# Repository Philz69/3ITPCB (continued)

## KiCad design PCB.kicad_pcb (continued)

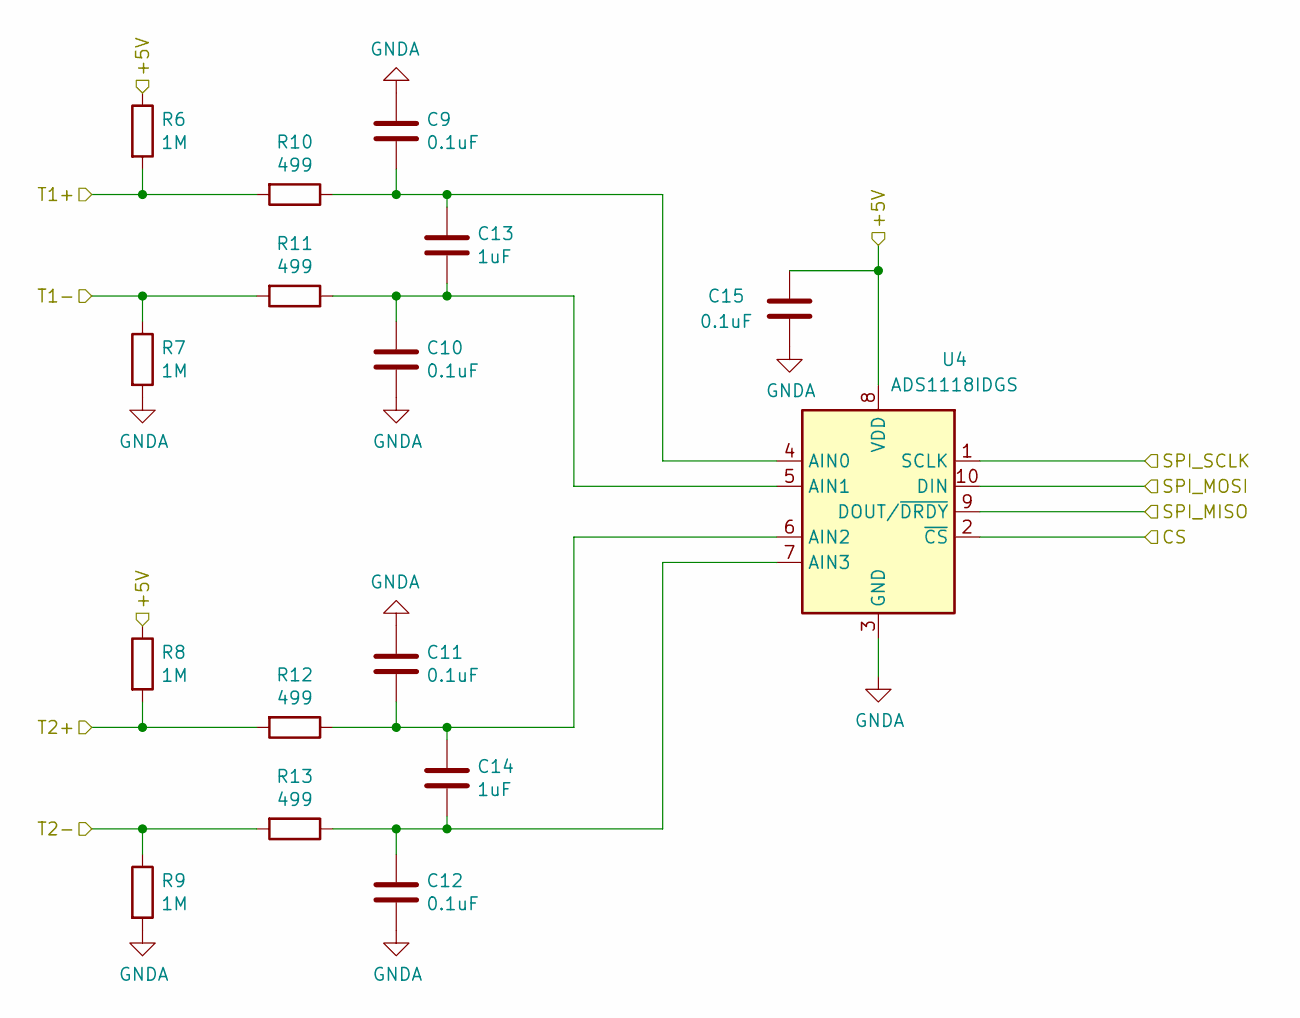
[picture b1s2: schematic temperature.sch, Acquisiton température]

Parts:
C9, C10, C11, C12, C15: 0.1uF; C_0402_1005Metric
C13, C14: 1uF; C_0402_1005Metric
R6, R7, R8, R9: 1M; R_0805_2012Metric
R10, R11, R12, R13: 499; R_0603_1608Metric
U4: ADS1118IDGS; VSSOP-10_3x3mm_P0.5mm

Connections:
/+5V: C15.2, R6.1, R8.1, U4.8 (VDD); also elsewhere on the board
/CS1: U4.2 (~CS); also elsewhere on the board
/MISO: U4.9 (DOUT/~DRDY); also elsewhere on the board
/MOSI: U4.10 (DIN); also elsewhere on the board
/SCK: U4.1 (SCLK); also elsewhere on the board
/T1+: R6.2, R10.2; also elsewhere on the board
/T1-: R7.1, R11.2; also elsewhere on the board
/T2+: R8.2, R12.2; also elsewhere on the board
/T2-: R9.1, R13.2; also elsewhere on the board
GNDA: C9.2, C10.2, C11.2, C12.2, C15.1, R7.2, R9.2, U4.3 (GND); also elsewhere on the board
unnamed: C10.1, C13.2, R11.1, U4.5 (AIN1)
unnamed: C11.1, C14.1, R12.1, U4.6 (AIN2)
unnamed: C12.1, C14.2, R13.1, U4.7 (AIN3)
unnamed: C9.1, C13.1, R10.1, U4.4 (AIN0)

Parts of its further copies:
C16, C17, C18, C19, C22, C23, C24, C25, C26, C29, C30, C31, C32, C33, C36, C71, C72, C73, C74, C77, C78, C79, C80, C81, C84, C85, C86, C87, C88, C91, C92, C93, C94, C95, C98: 0.1uF; C_0402_1005Metric
C20, C21, C27, C28, C34, C35, C75, C76, C82, C83, C89, C90, C96, C97: 1uF; C_0402_1005Metric
R14, R15, R16, R17, R22, R23, R24, R25, R30, R31, R32, R33, R94, R95, R96, R97, R102, R103, R104, R105, R110, R111, R112, R113, R118, R119, R120, R121: 1M; R_0805_2012Metric
R18, R19, R20, R21, R26, R27, R28, R29, R34, R35, R36, R37, R98, R99, R100, R101, R106, R107, R108, R109, R114, R115, R116, R117, R122, R123, R124, R125: 499; R_0603_1608Metric
U5, U6, U7, U32, U33, U34, U35: ADS1118IDGS; VSSOP-10_3x3mm_P0.5mm

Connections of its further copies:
/+5V: C22.2, C29.2, C36.2, C77.2, C84.2, C91.2, C98.2, R14.1, R16.1, R22.1, R24.1, R30.1, R32.1, R94.1, R96.1, R102.1, R104.1, R110.1, R112.1, R118.1, R120.1, U5.8 (VDD), U6.8 (VDD), U7.8 (VDD), U32.8 (VDD), U33.8 (VDD), U34.8 (VDD), U35.8 (VDD); also elsewhere on the board
/CS2: U5.2 (~CS); also elsewhere on the board
/CS3: U6.2 (~CS); also elsewhere on the board
/CS4: U7.2 (~CS); also elsewhere on the board
/CS5: U32.2 (~CS); also elsewhere on the board
/CS6: U33.2 (~CS); also elsewhere on the board
/CS7: U34.2 (~CS); also elsewhere on the board
/CS8: U35.2 (~CS); also elsewhere on the board
/MISO: U5.9 (DOUT/~DRDY), U6.9 (DOUT/~DRDY), U7.9 (DOUT/~DRDY), U32.9 (DOUT/~DRDY), U33.9 (DOUT/~DRDY), U34.9 (DOUT/~DRDY), U35.9 (DOUT/~DRDY); also elsewhere on the board
/MOSI: U5.10 (DIN), U6.10 (DIN), U7.10 (DIN), U32.10 (DIN), U33.10 (DIN), U34.10 (DIN), U35.10 (DIN); also elsewhere on the board
/SCK: U5.1 (SCLK), U6.1 (SCLK), U7.1 (SCLK), U32.1 (SCLK), U33.1 (SCLK), U34.1 (SCLK), U35.1 (SCLK); also elsewhere on the board
/T3+: R14.2, R18.2; also elsewhere on the board
/T3-: R15.1, R19.2; also elsewhere on the board
/T4+: R16.2, R20.2; also elsewhere on the board
/T4-: R17.1, R21.2; also elsewhere on the board
/T5+: R22.2, R26.2; also elsewhere on the board
/T5-: R23.1, R27.2; also elsewhere on the board
/T6+: R24.2, R28.2; also elsewhere on the board
/T6-: R25.1, R29.2; also elsewhere on the board
/T7+: R30.2, R34.2; also elsewhere on the board
/T7-: R31.1, R35.2; also elsewhere on the board
/T8+: R32.2, R36.2; also elsewhere on the board
/T8-: R33.1, R37.2; also elsewhere on the board
/T9+: R94.2, R98.2; also elsewhere on the board
/T9-: R95.1, R99.2; also elsewhere on the board
/T10+: R96.2, R100.2; also elsewhere on the board
/T10-: R97.1, R101.2; also elsewhere on the board
/T11+: R102.2, R106.2; also elsewhere on the board
/T11-: R103.1, R107.2; also elsewhere on the board
/T12+: R104.2, R108.2; also elsewhere on the board
/T12-: R105.1, R109.2; also elsewhere on the board
/T13+: R110.2, R114.2; also elsewhere on the board
/T13-: R111.1, R115.2; also elsewhere on the board
/T14+: R112.2, R116.2; also elsewhere on the board
/T14-: R113.1, R117.2; also elsewhere on the board
/T15+: R118.2, R122.2; also elsewhere on the board
/T15-: R119.1, R123.2; also elsewhere on the board
/T16+: R120.2, R124.2; also elsewhere on the board
/T16-: R121.1, R125.2; also elsewhere on the board
GNDA: C16.2, C17.2, C18.2, C19.2, C22.1, C23.2, C24.2, C25.2, C26.2, C29.1, C30.2, C31.2, C32.2, C33.2, C36.1, C71.2, C72.2, C73.2, C74.2, C77.1, C78.2, C79.2, C80.2, C81.2, C84.1, C85.2, C86.2, C87.2, C88.2, C91.1, C92.2, C93.2, C94.2, C95.2, C98.1, R15.2, R17.2, R23.2, R25.2, R31.2, R33.2, R95.2, R97.2, R103.2, R105.2, R111.2, R113.2, R119.2, R121.2, U5.3 (GND), U6.3 (GND), U7.3 (GND), U32.3 (GND), U33.3 (GND), U34.3 (GND), U35.3 (GND); also elsewhere on the board
unnamed: C16.1, C20.1, R18.1, U5.4 (AIN0)
unnamed: C17.1, C20.2, R19.1, U5.5 (AIN1)
unnamed: C18.1, C21.1, R20.1, U5.6 (AIN2)
unnamed: C19.1, C21.2, R21.1, U5.7 (AIN3)
unnamed: C23.1, C27.1, R26.1, U6.4 (AIN0)
unnamed: C24.1, C27.2, R27.1, U6.5 (AIN1)
unnamed: C25.1, C28.1, R28.1, U6.6 (AIN2)
unnamed: C26.1, C28.2, R29.1, U6.7 (AIN3)
unnamed: C30.1, C34.1, R34.1, U7.4 (AIN0)
unnamed: C31.1, C34.2, R35.1, U7.5 (AIN1)
unnamed: C32.1, C35.1, R36.1, U7.6 (AIN2)
unnamed: C33.1, C35.2, R37.1, U7.7 (AIN3)
unnamed: C71.1, C75.1, R98.1, U32.4 (AIN0)
unnamed: C72.1, C75.2, R99.1, U32.5 (AIN1)
unnamed: C73.1, C76.1, R100.1, U32.6 (AIN2)
unnamed: C74.1, C76.2, R101.1, U32.7 (AIN3)
unnamed: C78.1, C82.1, R106.1, U33.4 (AIN0)
unnamed: C79.1, C82.2, R107.1, U33.5 (AIN1)
unnamed: C80.1, C83.1, R108.1, U33.6 (AIN2)
unnamed: C81.1, C83.2, R109.1, U33.7 (AIN3)
unnamed: C85.1, C89.1, R114.1, U34.4 (AIN0)
unnamed: C86.1, C89.2, R115.1, U34.5 (AIN1)
unnamed: C87.1, C90.1, R116.1, U34.6 (AIN2)
unnamed: C88.1, C90.2, R117.1, U34.7 (AIN3)
unnamed: C92.1, C96.1, R122.1, U35.4 (AIN0)
unnamed: C93.1, C96.2, R123.1, U35.5 (AIN1)
unnamed: C94.1, C97.1, R124.1, U35.6 (AIN2)
unnamed: C95.1, C97.2, R125.1, U35.7 (AIN3)

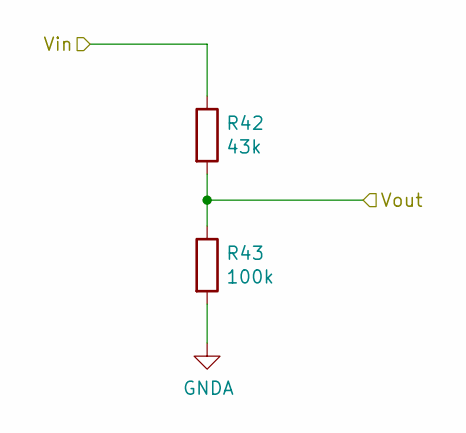
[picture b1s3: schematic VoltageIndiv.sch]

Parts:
R38: 43k; R_0805_2012Metric
R39: 100k; R_0805_2012Metric

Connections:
/A0: R38.2, R39.1; also elsewhere on the board
/VinPassif1: R38.1; also elsewhere on the board
GNDA: R39.2; also elsewhere on the board

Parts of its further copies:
R40, R42, R44, R46, R48, R50, R52, R66, R68, R70, R72, R74, R76, R78, R80: 43k; R_0805_2012Metric
R41, R43, R45, R47, R49, R51, R53, R67, R69, R71, R73, R75, R77, R79, R81: 100k; R_0805_2012Metric

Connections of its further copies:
/A1: R40.2, R41.1; also elsewhere on the board
/A2: R42.2, R43.1; also elsewhere on the board
/A3: R44.2, R45.1; also elsewhere on the board
/A4: R46.2, R47.1; also elsewhere on the board
/A5: R48.2, R49.1; also elsewhere on the board
/A6: R50.2, R51.1; also elsewhere on the board
/A7: R52.2, R53.1; also elsewhere on the board
/A8: R66.2, R67.1; also elsewhere on the board
/A9: R68.2, R69.1; also elsewhere on the board
/A10: R70.2, R71.1; also elsewhere on the board
/A11: R72.2, R73.1; also elsewhere on the board
/A12: R74.2, R75.1; also elsewhere on the board
/A13: R76.2, R77.1; also elsewhere on the board
/A14: R78.2, R79.1; also elsewhere on the board
/A15: R80.2, R81.1; also elsewhere on the board
/VinActif1: R66.1; also elsewhere on the board
/VinActif2: R68.1; also elsewhere on the board
/VinActif3: R70.1; also elsewhere on the board
/VinActif4: R72.1; also elsewhere on the board
/VinActif5: R74.1; also elsewhere on the board
/VinActif6: R76.1; also elsewhere on the board
/VinActif7: R78.1; also elsewhere on the board
/VinActif8: R80.1; also elsewhere on the board
/VinPassif2: R40.1; also elsewhere on the board
/VinPassif3: R42.1; also elsewhere on the board
/VinPassif4: R44.1; also elsewhere on the board
/VinPassif5: R46.1; also elsewhere on the board
/VinPassif6: R48.1; also elsewhere on the board
/VinPassif7: R50.1; also elsewhere on the board
/VinPassif8: R52.1; also elsewhere on the board
GNDA: R41.2, R43.2, R45.2, R47.2, R49.2, R51.2, R53.2, R67.2, R69.2, R71.2, R73.2, R75.2, R77.2, R79.2, R81.2; also elsewhere on the board

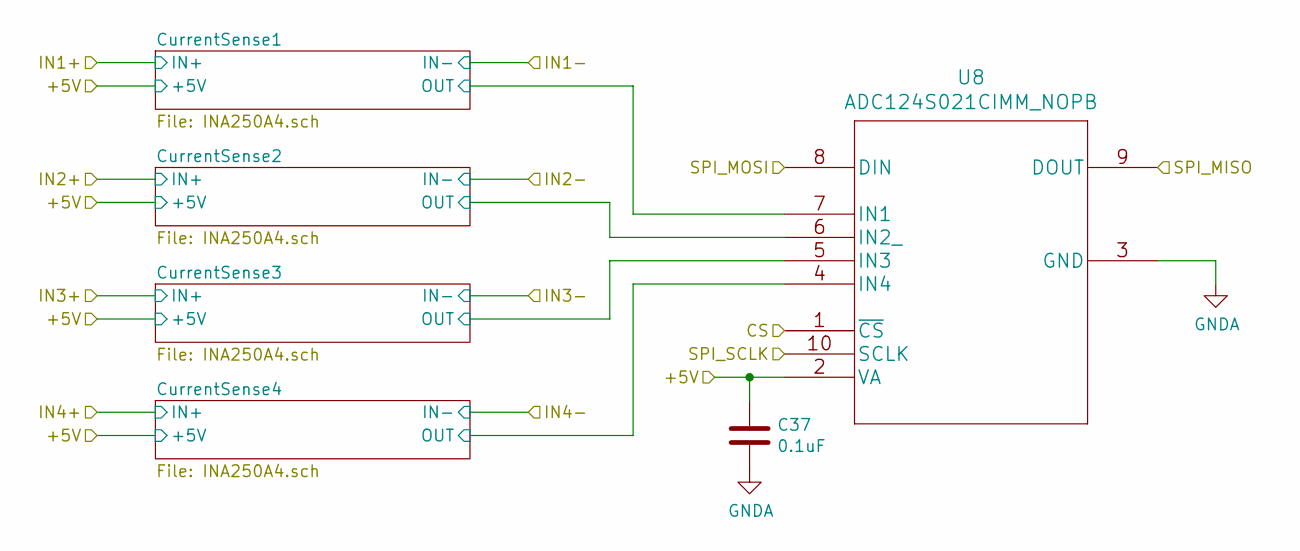
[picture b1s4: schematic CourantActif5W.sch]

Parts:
C52: 0.1uF; C_0402_1005Metric
U23: ADC124S021CIMM_NOPB; VSSOP-10_3x3mm_P0.5mm

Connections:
/+5V: C52.1, U23.2 (VA); also elsewhere on the board
/CS9: U23.1 (~CS); also elsewhere on the board
/CourantIndiv1/CurrentSense1/OUT: U23.7 (IN1); also elsewhere on the board
/CourantIndiv1/CurrentSense2/OUT: U23.6 (IN2_); also elsewhere on the board
/CourantIndiv1/CurrentSense3/OUT: U23.5 (IN3); also elsewhere on the board
/CourantIndiv1/CurrentSense4/OUT: U23.4 (IN4); also elsewhere on the board
/MISO: U23.9 (DOUT); also elsewhere on the board
/MOSI: U23.8 (DIN); also elsewhere on the board
/SCK: U23.10 (SCLK); also elsewhere on the board
GNDA: C52.2, U23.3 (GND); also elsewhere on the board

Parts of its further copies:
C37, C42, C47: 0.1uF; C_0402_1005Metric
U8, U13, U18: ADC124S021CIMM_NOPB; VSSOP-10_3x3mm_P0.5mm

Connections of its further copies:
/+5V: C37.1, C42.1, C47.1, U8.2 (VA), U13.2 (VA), U18.2 (VA); also elsewhere on the board
/CS10: U8.1 (~CS); also elsewhere on the board
/CS11: U13.1 (~CS); also elsewhere on the board
/CS12: U18.1 (~CS); also elsewhere on the board
/CourantActif5W1/CurrentSense1/OUT: U13.7 (IN1); also elsewhere on the board
/CourantActif5W1/CurrentSense2/OUT: U13.6 (IN2_); also elsewhere on the board
/CourantActif5W1/CurrentSense3/OUT: U13.5 (IN3); also elsewhere on the board
/CourantActif5W1/CurrentSense4/OUT: U13.4 (IN4); also elsewhere on the board
/CourantActif5W2/CurrentSense1/OUT: U18.7 (IN1); also elsewhere on the board
/CourantActif5W2/CurrentSense2/OUT: U18.6 (IN2_); also elsewhere on the board
/CourantActif5W2/CurrentSense3/OUT: U18.5 (IN3); also elsewhere on the board
/CourantActif5W2/CurrentSense4/OUT: U18.4 (IN4); also elsewhere on the board
/CourantIndiv2/CurrentSense1/OUT: U8.7 (IN1); also elsewhere on the board
/CourantIndiv2/CurrentSense2/OUT: U8.6 (IN2_); also elsewhere on the board
/CourantIndiv2/CurrentSense3/OUT: U8.5 (IN3); also elsewhere on the board
/CourantIndiv2/CurrentSense4/OUT: U8.4 (IN4); also elsewhere on the board
/MISO: U8.9 (DOUT), U13.9 (DOUT), U18.9 (DOUT); also elsewhere on the board
/MOSI: U8.8 (DIN), U13.8 (DIN), U18.8 (DIN); also elsewhere on the board
/SCK: U8.10 (SCLK), U13.10 (SCLK), U18.10 (SCLK); also elsewhere on the board
GNDA: C37.2, C42.2, C47.2, U8.3 (GND), U13.3 (GND), U18.3 (GND); also elsewhere on the board

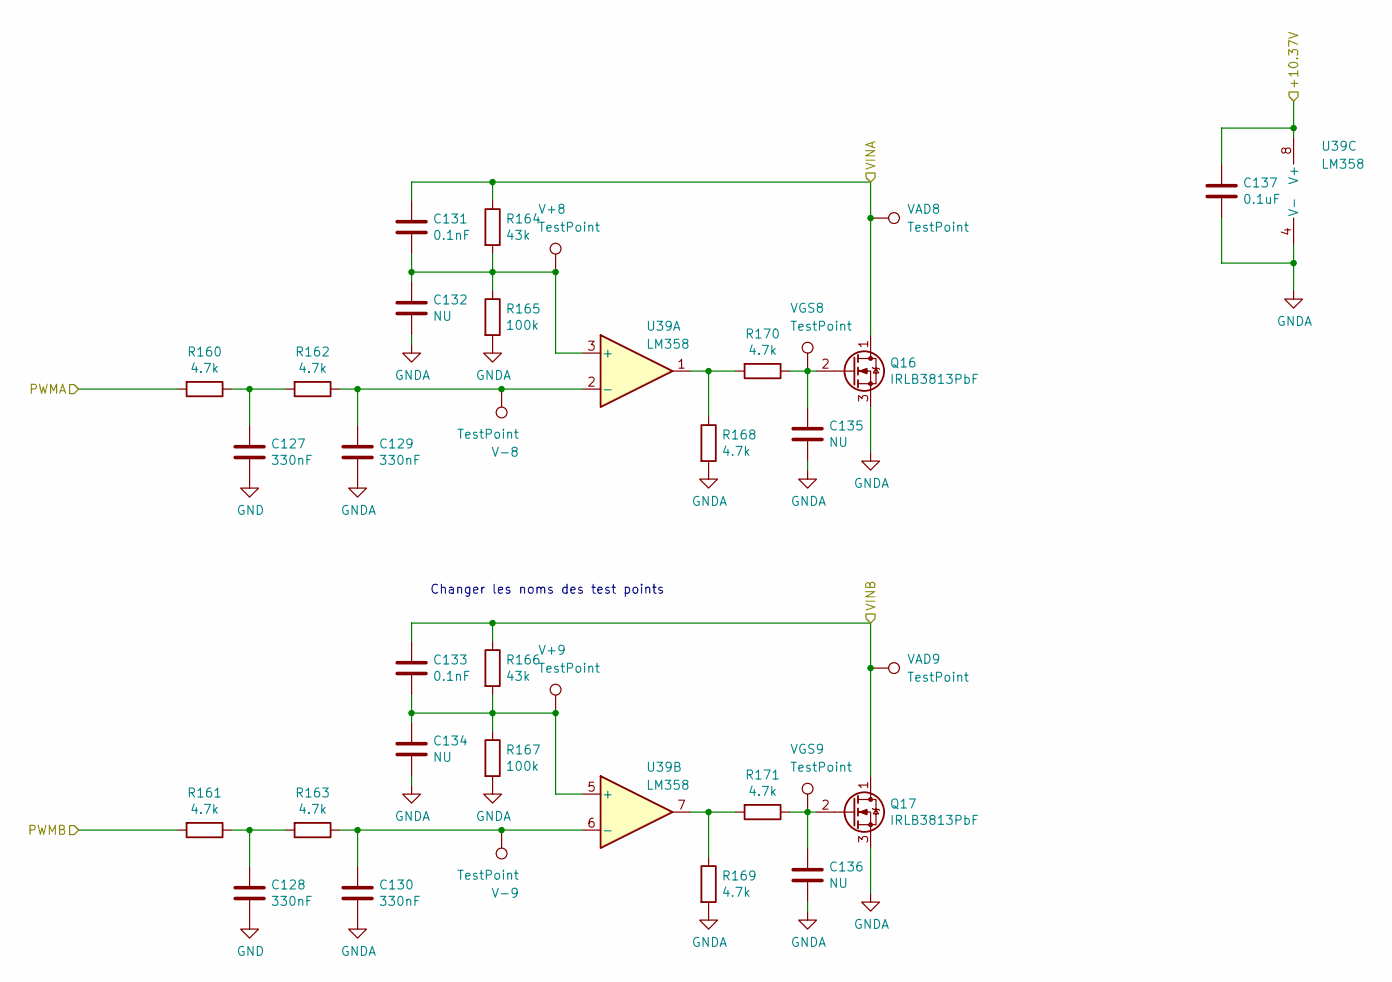
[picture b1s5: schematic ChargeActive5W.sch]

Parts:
C57, C58, C59, C60: 330nF; C_0603_1608Metric
C61, C63: 0.1nF; C_0402_1005Metric
C62, C64, C65, C66: NU; C_0402_1005Metric
C67: 0.1uF; C_0402_1005Metric
Q2, Q3: IRLB3813PbF; TO-220-3_Horizontal_TabDown_AccessHole
R54, R55, R56, R57, R62, R63, R64, R65: 4.7k; R_0805_2012Metric
R58, R60: 43k; R_0805_2012Metric
R59, R61: 100k; R_0805_2012Metric
U28: LM358; SOIC-8_3.9x4.9mm_P1.27mm
V+1, V+2: TestPoint; TestPoint_Pad_1.0x1.0mm
V-1, V-2: TestPoint; TestPoint_Pad_1.0x1.0mm
VAD1, VAD2: TestPoint; TestPoint_Pad_1.0x1.0mm
VGS1, VGS2: TestPoint; TestPoint_Pad_1.0x1.0mm

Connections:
/+10.37V: C67.2, U28.8 (V+); also elsewhere on the board
/PWM1: R54.2; also elsewhere on the board
/PWM2: R55.2; also elsewhere on the board
/VoutActif1: C61.2, Q2.1 (D), R58.1, VAD1.1; also elsewhere on the board
/VoutActif2: C63.2, Q3.1 (D), R60.1, VAD2.1; also elsewhere on the board
GND: C57.1, C58.1; also elsewhere on the board
GNDA: C59.1, C60.1, C62.1, C64.1, C65.1, C66.1, C67.1, Q2.3 (S), Q3.3 (S), R59.2, R61.2, R62.2, R63.2, U28.4 (V-); also elsewhere on the board
unnamed: C57.2, R54.1, R56.2
unnamed: C58.2, R55.1, R57.2
unnamed: C59.2, R56.1, U28.2 (-), V-1.1
unnamed: C60.2, R57.1, U28.6 (-), V-2.1
unnamed: C61.1, C62.2, R58.2, R59.1, U28.3 (+), V+1.1
unnamed: C63.1, C64.2, R60.2, R61.1, U28.5 (+), V+2.1
unnamed: C65.2, Q2.2 (G), R64.1, VGS1.1
unnamed: C66.2, Q3.2 (G), R65.1, VGS2.1
unnamed: R62.1, R64.2, U28.1
unnamed: R63.1, R65.2, U28.7

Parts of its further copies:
C105, C106, C107, C108, C116, C117, C118, C119, C127, C128, C129, C130: 330nF; C_0603_1608Metric
C109, C111, C120, C122, C131, C133: 0.1nF; C_0402_1005Metric
C110, C112, C113, C114, C121, C123, C124, C125, C132, C134, C135, C136: NU; C_0402_1005Metric
C115, C126, C137: 0.1uF; C_0402_1005Metric
Q12, Q13, Q14, Q15, Q16, Q17: IRLB3813PbF; TO-220-3_Horizontal_TabDown_AccessHole
R136, R137, R138, R139, R144, R145, R146, R147, R148, R149, R150, R151, R156, R157, R158, R159, R160, R161, R162, R163, R168, R169, R170, R171: 4.7k; R_0805_2012Metric
R140, R142, R152, R154, R164, R166: 43k; R_0805_2012Metric
R141, R143, R153, R155, R165, R167: 100k; R_0805_2012Metric
U37, U38, U39: LM358; SOIC-8_3.9x4.9mm_P1.27mm
V+4, V+5, V+6, V+7, V+8, V+9: TestPoint; TestPoint_Pad_1.0x1.0mm
V-4, V-5, V-6, V-7, V-8, V-9: TestPoint; TestPoint_Pad_1.0x1.0mm
VAD4, VAD5, VAD6, VAD7, VAD8, VAD9: TestPoint; TestPoint_Pad_1.0x1.0mm
VGS4, VGS5, VGS6, VGS7, VGS8, VGS9: TestPoint; TestPoint_Pad_1.0x1.0mm

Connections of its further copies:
/+10.37V: C115.2, C126.2, C137.2, U37.8 (V+), U38.8 (V+), U39.8 (V+); also elsewhere on the board
/PWM3: R136.2; also elsewhere on the board
/PWM4: R137.2; also elsewhere on the board
/PWM5: R148.2; also elsewhere on the board
/PWM6: R149.2; also elsewhere on the board
/PWM7: R160.2; also elsewhere on the board
/PWM8: R161.2; also elsewhere on the board
/VoutActif3: C109.2, Q12.1 (D), R140.1, VAD4.1; also elsewhere on the board
/VoutActif4: C111.2, Q13.1 (D), R142.1, VAD5.1; also elsewhere on the board
/VoutActif5: C120.2, Q14.1 (D), R152.1, VAD6.1; also elsewhere on the board
/VoutActif6: C122.2, Q15.1 (D), R154.1, VAD7.1; also elsewhere on the board
/VoutActif7: C131.2, Q16.1 (D), R164.1, VAD8.1; also elsewhere on the board
/VoutActif8: C133.2, Q17.1 (D), R166.1, VAD9.1; also elsewhere on the board
GND: C105.1, C106.1, C116.1, C117.1, C127.1, C128.1; also elsewhere on the board
GNDA: C107.1, C108.1, C110.1, C112.1, C113.1, C114.1, C115.1, C118.1, C119.1, C121.1, C123.1, C124.1, C125.1, C126.1, C129.1, C130.1, C132.1, C134.1, C135.1, C136.1, C137.1, Q12.3 (S), Q13.3 (S), Q14.3 (S), Q15.3 (S), Q16.3 (S), Q17.3 (S), R141.2, R143.2, R144.2, R145.2, R153.2, R155.2, R156.2, R157.2, R165.2, R167.2, R168.2, R169.2, U37.4 (V-), U38.4 (V-), U39.4 (V-); also elsewhere on the board
unnamed: C105.2, R136.1, R138.2
unnamed: C106.2, R137.1, R139.2
unnamed: C107.2, R138.1, U37.2 (-), V-4.1
unnamed: C108.2, R139.1, U37.6 (-), V-5.1
unnamed: C109.1, C110.2, R140.2, R141.1, U37.3 (+), V+4.1
unnamed: C111.1, C112.2, R142.2, R143.1, U37.5 (+), V+5.1
unnamed: C113.2, Q12.2 (G), R146.1, VGS4.1
unnamed: C114.2, Q13.2 (G), R147.1, VGS5.1
unnamed: C116.2, R148.1, R150.2
unnamed: C117.2, R149.1, R151.2
unnamed: C118.2, R150.1, U38.2 (-), V-6.1
unnamed: C119.2, R151.1, U38.6 (-), V-7.1
unnamed: C120.1, C121.2, R152.2, R153.1, U38.3 (+), V+6.1
unnamed: C122.1, C123.2, R154.2, R155.1, U38.5 (+), V+7.1
unnamed: C124.2, Q14.2 (G), R158.1, VGS6.1
unnamed: C125.2, Q15.2 (G), R159.1, VGS7.1
unnamed: C127.2, R160.1, R162.2
unnamed: C128.2, R161.1, R163.2
unnamed: C129.2, R162.1, U39.2 (-), V-8.1
unnamed: C130.2, R163.1, U39.6 (-), V-9.1
unnamed: C131.1, C132.2, R164.2, R165.1, U39.3 (+), V+8.1
unnamed: C133.1, C134.2, R166.2, R167.1, U39.5 (+), V+9.1
unnamed: C135.2, Q16.2 (G), R170.1, VGS8.1
unnamed: C136.2, Q17.2 (G), R171.1, VGS9.1
unnamed: R144.1, R146.2, U37.1
unnamed: R145.1, R147.2, U37.7
unnamed: R156.1, R158.2, U38.1
unnamed: R157.1, R159.2, U38.7
unnamed: R168.1, R170.2, U39.1
unnamed: R169.1, R171.2, U39.7

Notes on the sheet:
Changer les noms des test points

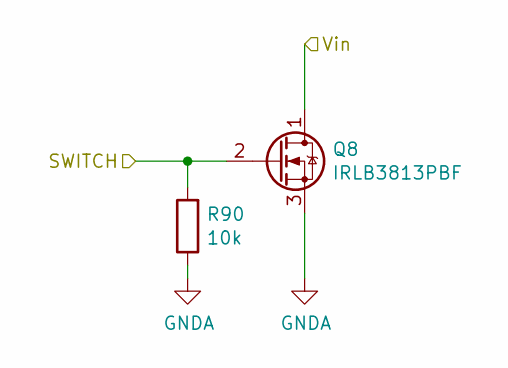
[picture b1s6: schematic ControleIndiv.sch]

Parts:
Q4: IRLB3813PBF; TO-220-3_Horizontal_TabDown_AccessHole
R82: 10k; R_0603_1608Metric

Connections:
/SW1: Q4.2 (G), R82.2; also elsewhere on the board
/VoutPassif1: Q4.1 (D); also elsewhere on the board
GNDA: Q4.3 (S), R82.1; also elsewhere on the board

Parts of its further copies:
Q5, Q6, Q7, Q8, Q9, Q10, Q11: IRLB3813PBF; TO-220-3_Horizontal_TabDown_AccessHole
R87, R88, R89, R90, R91, R92, R93: 10k; R_0603_1608Metric

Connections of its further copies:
/SW2: Q5.2 (G), R87.2; also elsewhere on the board
/SW3: Q6.2 (G), R88.2; also elsewhere on the board
/SW4: Q7.2 (G), R89.2; also elsewhere on the board
/SW5: Q8.2 (G), R90.2; also elsewhere on the board
/SW6: Q9.2 (G), R91.2; also elsewhere on the board
/SW7: Q10.2 (G), R92.2; also elsewhere on the board
/SW8: Q11.2 (G), R93.2; also elsewhere on the board
/VoutPassif2: Q5.1 (D); also elsewhere on the board
/VoutPassif3: Q6.1 (D); also elsewhere on the board
/VoutPassif4: Q7.1 (D); also elsewhere on the board
/VoutPassif5: Q8.1 (D); also elsewhere on the board
/VoutPassif6: Q9.1 (D); also elsewhere on the board
/VoutPassif7: Q10.1 (D); also elsewhere on the board
/VoutPassif8: Q11.1 (D); also elsewhere on the board
GNDA: Q5.3 (S), Q6.3 (S), Q7.3 (S), Q8.3 (S), Q9.3 (S), Q10.3 (S), Q11.3 (S), R87.1, R88.1, R89.1, R90.1, R91.1, R92.1, R93.1; also elsewhere on the board

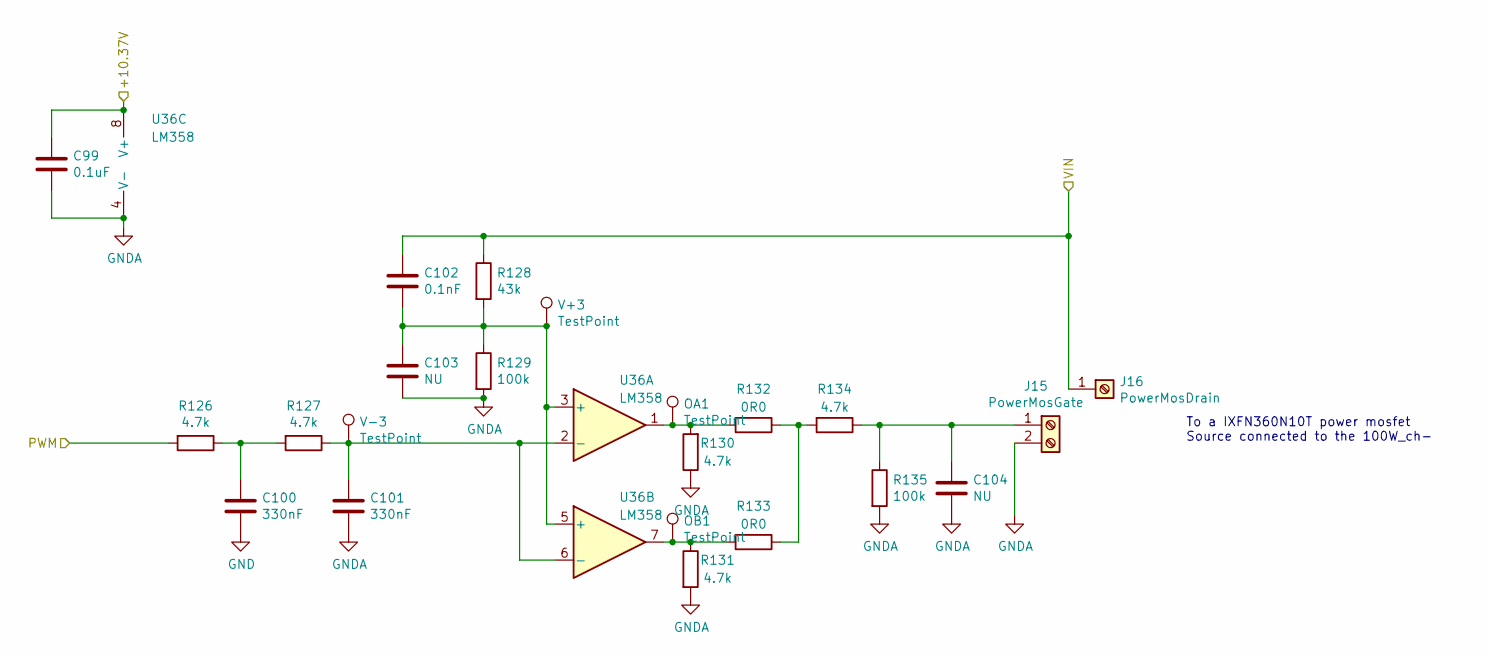
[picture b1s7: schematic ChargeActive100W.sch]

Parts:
C99: 0.1uF; C_0402_1005Metric
C100, C101: 330nF; C_0603_1608Metric
C102: 0.1nF; C_0402_1005Metric
C103, C104: NU; C_0402_1005Metric
J15: PowerMosGate; TerminalBlock_Phoenix_PT-1,5-2-5.0-H_1x02_P5.00mm_Horizontal
J16: PowerMosDrain; 30ATerminal
OA1: TestPoint; TestPoint_Pad_1.0x1.0mm
OB1: TestPoint; TestPoint_Pad_1.0x1.0mm
R126, R127, R130, R131, R134: 4.7k; R_0805_2012Metric
R128: 43k; R_0805_2012Metric
R129, R135: 100k; R_0805_2012Metric
R132, R133: 0R0; R_0805_2012Metric
U36: LM358; SOIC-8_3.9x4.9mm_P1.27mm
V+3: TestPoint; TestPoint_Pad_1.0x1.0mm
V-3: TestPoint; TestPoint_Pad_1.0x1.0mm

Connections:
/+10.37V: C99.2, U36.8 (V+); also elsewhere on the board
/PWM9: R126.2; also elsewhere on the board
/VoutActif100W: C102.2, J16.1, R128.1; also elsewhere on the board
GND: C100.1; also elsewhere on the board
GNDA: C99.1, C101.1, C103.1, C104.1, J15.2, R129.2, R130.1, R131.2, R135.2, U36.4 (V-); also elsewhere on the board
unnamed: C100.2, R126.1, R127.2
unnamed: C101.2, R127.1, U36.2 (-), U36.6 (-), V-3.1
unnamed: C102.1, C103.2, R128.2, R129.1, U36.3 (+), U36.5 (+), V+3.1
unnamed: C104.2, J15.1, R134.1, R135.1
unnamed: OA1.1, R130.2, R132.2, U36.1
unnamed: OB1.1, R131.1, R133.2, U36.7
unnamed: R132.1, R133.1, R134.2

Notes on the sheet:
To a IXFN360N10T power mosfet Source connected to the 100W_ch-

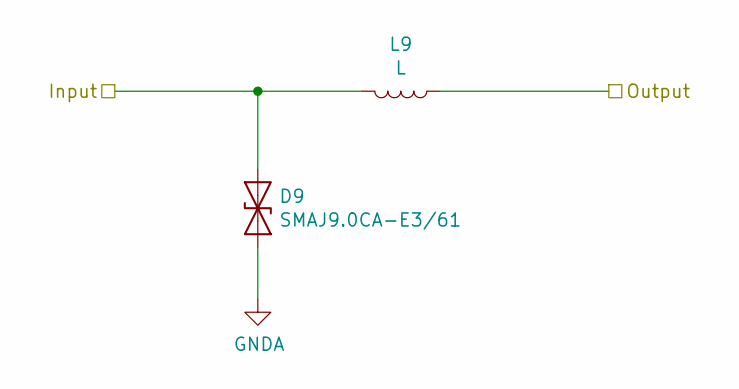
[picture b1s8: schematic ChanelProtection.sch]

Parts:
D2: SMAJ9.0CA-E3/61; D_SMA
L2: L; TraceInductor

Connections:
/AIProt1/Input: D2.1 (A1), L2.2; also elsewhere on the board
/VinPassif1: L2.1; also elsewhere on the board
GNDA: D2.2 (A2); also elsewhere on the board

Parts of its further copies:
D3, D4, D5, D6, D7, D8, D9, D10, D11, D12, D13, D14, D15, D16, D17, D18, D19: SMAJ9.0CA-E3/61; D_SMA
L3, L4, L5, L6, L7, L8, L9, L10, L11, L12, L13, L14, L15, L16, L17, L18, L19: L; TraceInductor

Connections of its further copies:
/AIProt2/Input: D3.1 (A1), L3.2; also elsewhere on the board
/AIProt3/Input: D4.1 (A1), L4.2; also elsewhere on the board
/AIProt4/Input: D5.1 (A1), L5.2; also elsewhere on the board
/AIProt5/Input: D6.1 (A1), L6.2; also elsewhere on the board
/AIProt6/Input: D7.1 (A1), L7.2; also elsewhere on the board
/AIProt7/Input: D8.1 (A1), L8.2; also elsewhere on the board
/AIProt8/Input: D9.1 (A1), L9.2; also elsewhere on the board
/ProtectionActif1/Input: D10.1 (A1), L10.2; also elsewhere on the board
/ProtectionActif2/Input: D11.1 (A1), L11.2; also elsewhere on the board
/ProtectionActif3/Input: D12.1 (A1), L12.2; also elsewhere on the board
/ProtectionActif4/Input: D13.1 (A1), L13.2; also elsewhere on the board
/ProtectionActif5/Input: D14.1 (A1), L14.2; also elsewhere on the board
/ProtectionActif6/Input: D15.1 (A1), L15.2; also elsewhere on the board
/ProtectionActif7/Input: D16.1 (A1), L16.2; also elsewhere on the board
/ProtectionActif8/Input: D17.1 (A1), L17.2; also elsewhere on the board
/SenseProtection+/Input: D18.1 (A1), L18.2; also elsewhere on the board
/SenseProtection-/Input: D19.1 (A1), L19.2; also elsewhere on the board
/V+Sense100W: L18.1; also elsewhere on the board
/V-Sense100W: L19.1; also elsewhere on the board
/VinActif1: L10.1; also elsewhere on the board
/VinActif2: L11.1; also elsewhere on the board
/VinActif3: L12.1; also elsewhere on the board
/VinActif4: L13.1; also elsewhere on the board
/VinActif5: L14.1; also elsewhere on the board
/VinActif6: L15.1; also elsewhere on the board
/VinActif7: L16.1; also elsewhere on the board
/VinActif8: L17.1; also elsewhere on the board
/VinPassif2: L3.1; also elsewhere on the board
/VinPassif3: L4.1; also elsewhere on the board
/VinPassif4: L5.1; also elsewhere on the board
/VinPassif5: L6.1; also elsewhere on the board
/VinPassif6: L7.1; also elsewhere on the board
/VinPassif7: L8.1; also elsewhere on the board
/VinPassif8: L9.1; also elsewhere on the board
GNDA: D3.2 (A2), D4.2 (A2), D5.2 (A2), D6.2 (A2), D7.2 (A2), D8.2 (A2), D9.2 (A2), D10.2 (A2), D11.2 (A2), D12.2 (A2), D13.2 (A2), D14.2 (A2), D15.2 (A2), D16.2 (A2), D17.2 (A2), D18.2 (A2), D19.2 (A2); also elsewhere on the board

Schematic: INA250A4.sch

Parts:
C56: 0.1uF; C_0402_1005Metric
U27: INA250A4PW; TSSOP-16_4.4x5mm_P0.65mm

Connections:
/+5V: C56.1, U27.10 (VS); also elsewhere on the board
/CourantIndiv1/CurrentSense1/OUT: U27.9 (OUT); also elsewhere on the board
/VinPassif1: U27.14 (IN+), U27.15 (IN+), U27.16 (IN+); also elsewhere on the board
/VoutPassif1: U27.1 (IN-), U27.2 (IN-), U27.3 (IN-); also elsewhere on the board
GNDA: C56.2, U27.6 (GND), U27.7 (REF), U27.8 (GND), U27.11 (GND); also elsewhere on the board
unnamed: U27.4 (SH-), U27.5 (VIN-)
unnamed: U27.12 (VIN+), U27.13 (SH+)

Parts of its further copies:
C38, C39, C40, C41, C43, C44, C45, C46, C48, C49, C50, C51, C53, C54, C55: 0.1uF; C_0402_1005Metric
U9, U10, U11, U12, U14, U15, U16, U17, U19, U20, U21, U22, U24, U25, U26: INA250A4PW; TSSOP-16_4.4x5mm_P0.65mm

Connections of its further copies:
/+5V: C38.1, C39.1, C40.1, C41.1, C43.1, C44.1, C45.1, C46.1, C48.1, C49.1, C50.1, C51.1, C53.1, C54.1, C55.1, U9.10 (VS), U10.10 (VS), U11.10 (VS), U12.10 (VS), U14.10 (VS), U15.10 (VS), U16.10 (VS), U17.10 (VS), U19.10 (VS), U20.10 (VS), U21.10 (VS), U22.10 (VS), U24.10 (VS), U25.10 (VS), U26.10 (VS); also elsewhere on the board
/CourantActif5W1/CurrentSense1/OUT: U17.9 (OUT); also elsewhere on the board
/CourantActif5W1/CurrentSense2/OUT: U14.9 (OUT); also elsewhere on the board
/CourantActif5W1/CurrentSense3/OUT: U15.9 (OUT); also elsewhere on the board
/CourantActif5W1/CurrentSense4/OUT: U16.9 (OUT); also elsewhere on the board
/CourantActif5W2/CurrentSense1/OUT: U22.9 (OUT); also elsewhere on the board
/CourantActif5W2/CurrentSense2/OUT: U19.9 (OUT); also elsewhere on the board
/CourantActif5W2/CurrentSense3/OUT: U20.9 (OUT); also elsewhere on the board
/CourantActif5W2/CurrentSense4/OUT: U21.9 (OUT); also elsewhere on the board
/CourantIndiv1/CurrentSense2/OUT: U24.9 (OUT); also elsewhere on the board
/CourantIndiv1/CurrentSense3/OUT: U25.9 (OUT); also elsewhere on the board
/CourantIndiv1/CurrentSense4/OUT: U26.9 (OUT); also elsewhere on the board
/CourantIndiv2/CurrentSense1/OUT: U12.9 (OUT); also elsewhere on the board
/CourantIndiv2/CurrentSense2/OUT: U9.9 (OUT); also elsewhere on the board
/CourantIndiv2/CurrentSense3/OUT: U10.9 (OUT); also elsewhere on the board
/CourantIndiv2/CurrentSense4/OUT: U11.9 (OUT); also elsewhere on the board
/VinActif1: U17.14 (IN+), U17.15 (IN+), U17.16 (IN+); also elsewhere on the board
/VinActif2: U14.14 (IN+), U14.15 (IN+), U14.16 (IN+); also elsewhere on the board
/VinActif3: U15.14 (IN+), U15.15 (IN+), U15.16 (IN+); also elsewhere on the board
/VinActif4: U16.14 (IN+), U16.15 (IN+), U16.16 (IN+); also elsewhere on the board
/VinActif5: U22.14 (IN+), U22.15 (IN+), U22.16 (IN+); also elsewhere on the board
/VinActif6: U19.14 (IN+), U19.15 (IN+), U19.16 (IN+); also elsewhere on the board
/VinActif7: U20.14 (IN+), U20.15 (IN+), U20.16 (IN+); also elsewhere on the board
/VinActif8: U21.14 (IN+), U21.15 (IN+), U21.16 (IN+); also elsewhere on the board
/VinPassif2: U24.14 (IN+), U24.15 (IN+), U24.16 (IN+); also elsewhere on the board
/VinPassif3: U25.14 (IN+), U25.15 (IN+), U25.16 (IN+); also elsewhere on the board
/VinPassif4: U26.14 (IN+), U26.15 (IN+), U26.16 (IN+); also elsewhere on the board
/VinPassif5: U12.14 (IN+), U12.15 (IN+), U12.16 (IN+); also elsewhere on the board
/VinPassif6: U9.14 (IN+), U9.15 (IN+), U9.16 (IN+); also elsewhere on the board
/VinPassif7: U10.14 (IN+), U10.15 (IN+), U10.16 (IN+); also elsewhere on the board
/VinPassif8: U11.14 (IN+), U11.15 (IN+), U11.16 (IN+); also elsewhere on the board
/VoutActif1: U17.1 (IN-), U17.2 (IN-), U17.3 (IN-); also elsewhere on the board
/VoutActif2: U14.1 (IN-), U14.2 (IN-), U14.3 (IN-); also elsewhere on the board
/VoutActif3: U15.1 (IN-), U15.2 (IN-), U15.3 (IN-); also elsewhere on the board
/VoutActif4: U16.1 (IN-), U16.2 (IN-), U16.3 (IN-); also elsewhere on the board
/VoutActif5: U22.1 (IN-), U22.2 (IN-), U22.3 (IN-); also elsewhere on the board
/VoutActif6: U19.1 (IN-), U19.2 (IN-), U19.3 (IN-); also elsewhere on the board
/VoutActif7: U20.1 (IN-), U20.2 (IN-), U20.3 (IN-); also elsewhere on the board
/VoutActif8: U21.1 (IN-), U21.2 (IN-), U21.3 (IN-); also elsewhere on the board
/VoutPassif2: U24.1 (IN-), U24.2 (IN-), U24.3 (IN-); also elsewhere on the board
/VoutPassif3: U25.1 (IN-), U25.2 (IN-), U25.3 (IN-); also elsewhere on the board
/VoutPassif4: U26.1 (IN-), U26.2 (IN-), U26.3 (IN-); also elsewhere on the board
/VoutPassif5: U12.1 (IN-), U12.2 (IN-), U12.3 (IN-); also elsewhere on the board
/VoutPassif6: U9.1 (IN-), U9.2 (IN-), U9.3 (IN-); also elsewhere on the board
/VoutPassif7: U10.1 (IN-), U10.2 (IN-), U10.3 (IN-); also elsewhere on the board
/VoutPassif8: U11.1 (IN-), U11.2 (IN-), U11.3 (IN-); also elsewhere on the board
GNDA: C38.2, C39.2, C40.2, C41.2, C43.2, C44.2, C45.2, C46.2, C48.2, C49.2, C50.2, C51.2, C53.2, C54.2, C55.2, U9.6 (GND), U9.7 (REF), U9.8 (GND), U9.11 (GND), U10.6 (GND), U10.7 (REF), U10.8 (GND), U10.11 (GND), U11.6 (GND), U11.7 (REF), U11.8 (GND), U11.11 (GND), U12.6 (GND), U12.7 (REF), U12.8 (GND), U12.11 (GND), U14.6 (GND), U14.7 (REF), U14.8 (GND), U14.11 (GND), U15.6 (GND), U15.7 (REF), U15.8 (GND), U15.11 (GND), U16.6 (GND), U16.7 (REF), U16.8 (GND), U16.11 (GND), U17.6 (GND), U17.7 (REF), U17.8 (GND), U17.11 (GND), U19.6 (GND), U19.7 (REF), U19.8 (GND), U19.11 (GND), U20.6 (GND), U20.7 (REF), U20.8 (GND), U20.11 (GND), U21.6 (GND), U21.7 (REF), U21.8 (GND), U21.11 (GND), U22.6 (GND), U22.7 (REF), U22.8 (GND), U22.11 (GND), U24.6 (GND), U24.7 (REF), U24.8 (GND), U24.11 (GND), U25.6 (GND), U25.7 (REF), U25.8 (GND), U25.11 (GND), U26.6 (GND), U26.7 (REF), U26.8 (GND), U26.11 (GND); also elsewhere on the board
unnamed: U9.4 (SH-), U9.5 (VIN-)
unnamed: U9.12 (VIN+), U9.13 (SH+)
unnamed: U10.4 (SH-), U10.5 (VIN-)
unnamed: U10.12 (VIN+), U10.13 (SH+)
unnamed: U11.4 (SH-), U11.5 (VIN-)
unnamed: U11.12 (VIN+), U11.13 (SH+)
unnamed: U12.4 (SH-), U12.5 (VIN-)
unnamed: U12.12 (VIN+), U12.13 (SH+)
unnamed: U14.4 (SH-), U14.5 (VIN-)
unnamed: U14.12 (VIN+), U14.13 (SH+)
unnamed: U15.4 (SH-), U15.5 (VIN-)
unnamed: U15.12 (VIN+), U15.13 (SH+)
unnamed: U16.4 (SH-), U16.5 (VIN-)
unnamed: U16.12 (VIN+), U16.13 (SH+)
unnamed: U17.4 (SH-), U17.5 (VIN-)
unnamed: U17.12 (VIN+), U17.13 (SH+)
unnamed: U19.4 (SH-), U19.5 (VIN-)
unnamed: U19.12 (VIN+), U19.13 (SH+)
unnamed: U20.4 (SH-), U20.5 (VIN-)
unnamed: U20.12 (VIN+), U20.13 (SH+)
unnamed: U21.4 (SH-), U21.5 (VIN-)
unnamed: U21.12 (VIN+), U21.13 (SH+)
unnamed: U22.4 (SH-), U22.5 (VIN-)
unnamed: U22.12 (VIN+), U22.13 (SH+)
unnamed: U24.4 (SH-), U24.5 (VIN-)
unnamed: U24.12 (VIN+), U24.13 (SH+)
unnamed: U25.4 (SH-), U25.5 (VIN-)
unnamed: U25.12 (VIN+), U25.13 (SH+)
unnamed: U26.4 (SH-), U26.5 (VIN-)
unnamed: U26.12 (VIN+), U26.13 (SH+)
